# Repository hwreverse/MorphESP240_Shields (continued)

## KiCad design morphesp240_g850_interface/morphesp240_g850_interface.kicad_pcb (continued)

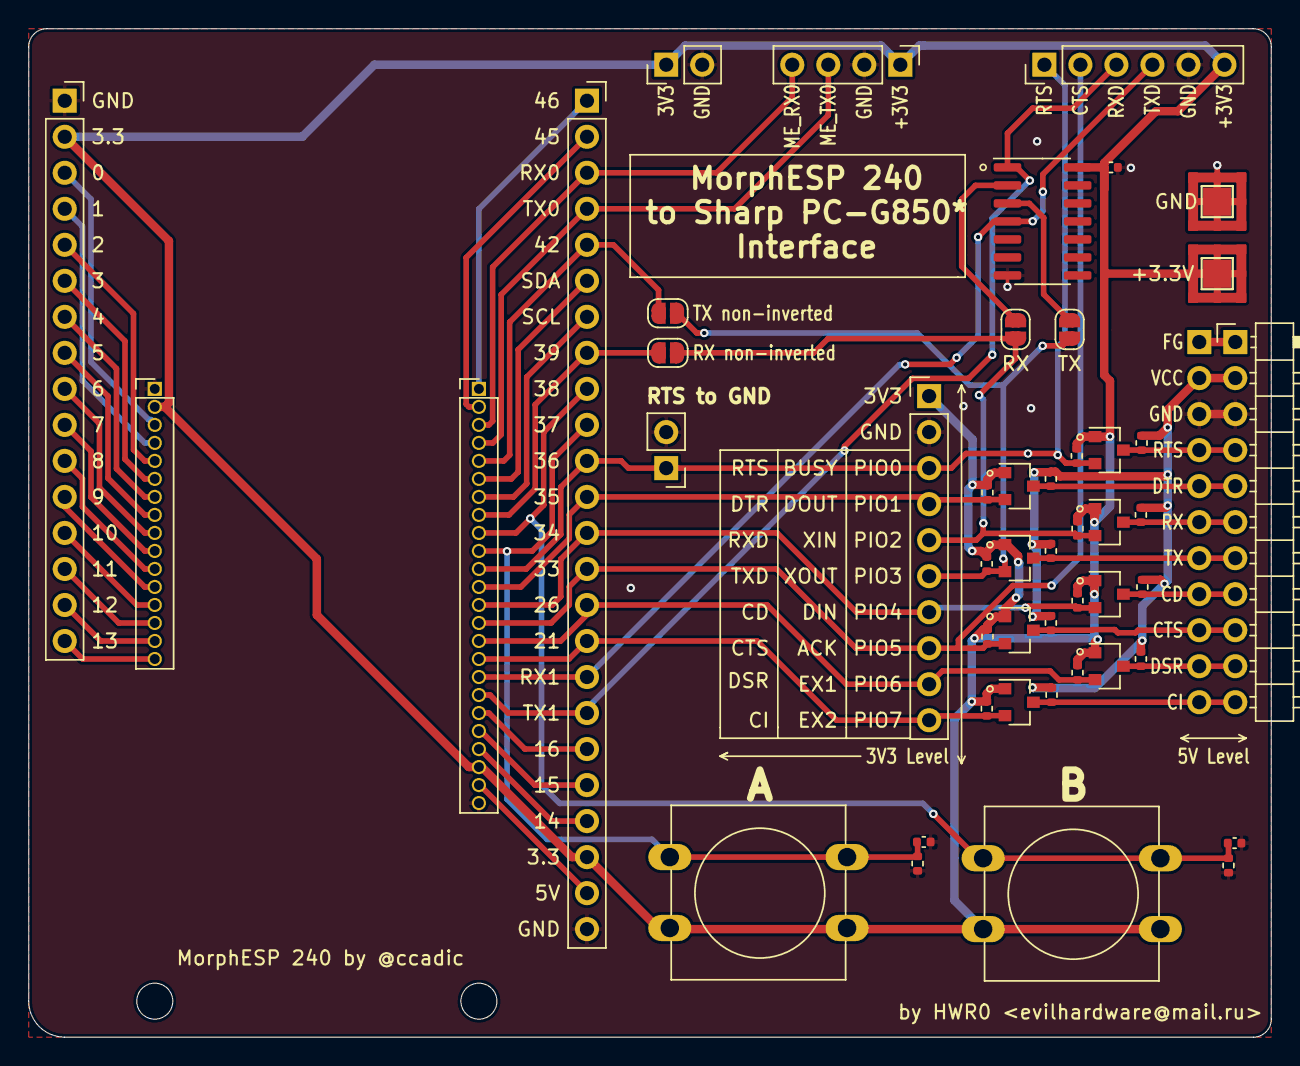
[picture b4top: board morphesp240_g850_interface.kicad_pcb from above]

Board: 2 copper layers, 87.6 x 71.1 mm, 49 parts (0 on the bottom side), 52 nets.

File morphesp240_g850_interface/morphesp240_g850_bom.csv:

Comment,Designator,Footprint,LCSC
"100nF","C1,C2,C3","Capacitor_SMD:C_0402_1005Metric","C1525"
"2.54P CNX","J1","Connector_PinSocket_2.54mm:PinSocket_1x24_P2.54mm_Vertical",""
"Conn_01x10_Male","J10","Connector_PinHeader_2.54mm:PinHeader_1x10_P2.54mm_Vertical",""
"3.3V Calculator Serial Output","J11","Connector_PinHeader_2.54mm:PinHeader_1x06_P2.54mm_Vertical",""
"CNDup","J12","hwreverse:BreadBoard_2.54mm_1x11",""
"Conn_01x11_Male","J13","Connector_PinHeader_2.54mm:PinHeader_1x11_P2.54mm_Horizontal",""
"1.27P CNX","J2","Socket_Strips:Socket_Strip_Straight_1x24_Pitch1.27mm",""
"1.27P CNX","J3","Socket_Strips:Socket_Strip_Straight_1x16_Pitch1.27mm",""
"2.54P CNX","J4","Connector_PinSocket_2.54mm:PinSocket_1x16_P2.54mm_Vertical",""
"3.3V Connector","J6","Connector_PinHeader_2.54mm:PinHeader_1x02_P2.54mm_Vertical",""
"SolidPad-Connector","J5,J7","hwreverse:SolidPad_4x4mm_2x2mmCore",""
"Conn_01x04_Male","J8","Connector_PinHeader_2.54mm:PinHeader_1x04_P2.54mm_Vertical",""
"RTS to Ground Jumper","J9","Connector_PinHeader_2.54mm:PinHeader_1x02_P2.54mm_Vertical",""
"SolderJumper_2_Open","JPRXD1,JPTXD1,JPLTXD1,JPLRXD1","Jumper:SolderJumper-2_P1.3mm_Open_RoundedPad1.0x1.5mm",""
"BSS138","Q1,Q2,Q3,Q4,Q5,Q6,Q7,Q8","Package_TO_SOT_SMD:SOT-23","C52895"
"10K","R1,R2,R3,R4,R5,R6,R7,R8,R9,R10,R11,R12,R13,R14,R15,R16,R17,R18","Resistor_SMD:R_0402_1005Metric","C25744"
"Button A","SW1","Button_Switch_THT:SW_PUSH-12mm","C620359"
"Button B","SW2","Button_Switch_THT:SW_PUSH-12mm","C620359"
"74HC04D","U1","Package_SO:SOIC-14_3.9x8.7mm_P1.27mm","C5590"

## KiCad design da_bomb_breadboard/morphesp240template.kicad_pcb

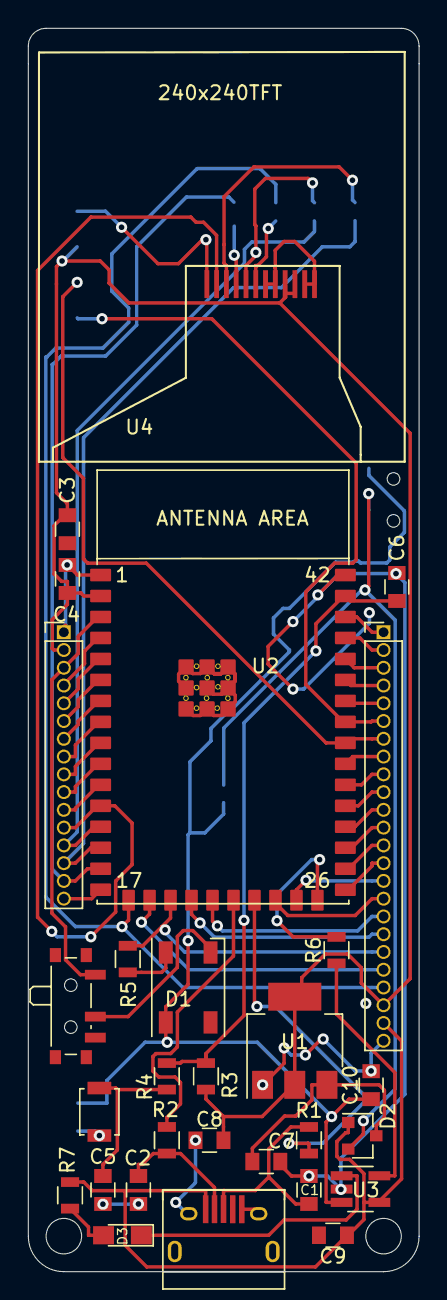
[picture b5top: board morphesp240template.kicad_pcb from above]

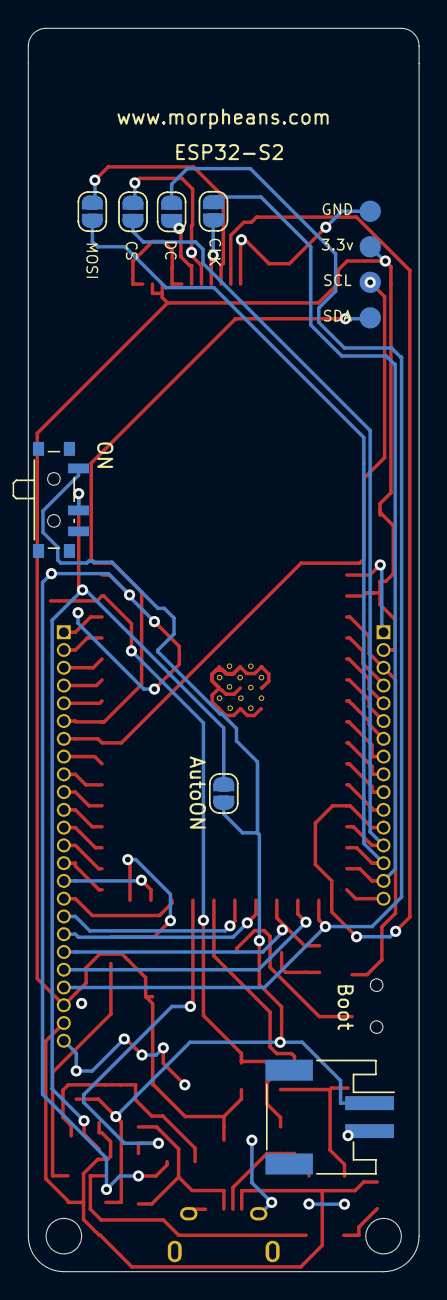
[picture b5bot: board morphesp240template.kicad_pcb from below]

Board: 2 copper layers, 27.9 x 88.9 mm, 37 parts (8 on the bottom side), 55 nets.

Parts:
C1, C2: 20pF; C_0805
C3, C5, C6: 100nF; C_0805
C4, C7, C8: 10uF; C_0805
C9, C10: 4.7uF; C_0805
D1: WS2812B; LED_WS2812B-PLCC4
D2: BAT54C; SOT-23
D3: Charge; LED_0805_HandSoldering
J1: USB_B_Mini; USB_Micro-B_HandSoldering
J2: Cnx1; Socket_Strip_Straight_1x16_Pitch1.27mm
J3: Con2; Socket_Strip_Straight_1x24_Pitch1.27mm
J4: Conn_01x02_Female; JST_PH_S2B-PH-SM4-TB_02x2.00mm_Angled
J5: i2C-v; 4cnx
JP1: CLK; JumperSmall
JP2: CS; JumperSmall
JP3: DC; JumperSmall
JP4: MOSI; JumperSmall
JP5: AutoON; JumperSmall
R1, R2, R4: 0R; R_0805
R3: 10k; R_0805
R5: 470; R_0805
R6: 2k; R_0805
R7: 470R; R_0805
SW1: SW_Push; SW_SPST_B3U-1000P
SW2: Boot; SW_SPDT_PCM12
SW3: ON; SW_SPDT_PCM12
U1: AP1117-33; SOT-223-3_TabPin2
U2: esp32-s2-wroom; esp32-s2-wrooom
U3: MCP73831-2-OT; SOT-23-5_HandSoldering
U4: 240x240TFT; 240240TFT

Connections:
/3.3v: C3.2, C4.2, C8.2, J2.2, J3.22, J5.3, R3.1, U1.2, U2.2, U4.3, U4.4
/D+: R1.1, U2.23
/D-: R2.1, U2.22
/DC_DISP: J3.21, JP3.1, U2.17
/EN: C6.2, R3.2, R4.1, U2.41
/IO0: J2.3, SW2.1, U2.3
/RGBLED: J3.19, R5.2, U2.19
/SCL: J3.7, J5.2, U2.34
/SDA: J3.6, J5.1, U2.35
/SPI_CLK: J2.15, JP1.1, U2.15
/SPI_CS: J2.13, JP2.1, U2.13
/SPI_MISO: J2.16, U2.16
/SPI_MOSI: J2.14, JP4.1, U2.14
/TFT_RESET: J2.12, U2.12, U4.11
/U1RXD: J3.17, U2.21
/U1TXD: J3.18, U2.20
/VBAT: C10.1, D1.1, J4.1, JP5.2, SW3.1, U3.3
/VUSB: C9.1, D2.1, J1.1, J3.23, R7.1, U3.4
GND: C1.2, C2.2, C3.1, C4.1, C5.2, C6.1, C7.1, C8.1, C9.2, C10.2, D1.3, J1.5, J1.6, J2.1, J3.24, J4.2, J5.4, R6.2, SW1.1, SW2.2, U1.1, U2.1, U2.26, U2.42, U2.43, U3.2, U4.1, U4.2, U4.5, U4.6, U4.12
unnamed: C1.1, J1.3, R1.2
unnamed: C2.1, J1.2, R2.2
unnamed: C5.1, R4.2, SW1.2
unnamed: C7.2, D2.3, U1.3
unnamed: D1.4, R5.1
unnamed: D2.2, JP5.1, SW3.2
unnamed: D3.1, U3.1
unnamed: D3.2, R7.2
unnamed: J2.4, U2.4
unnamed: J2.5, U2.5
unnamed: J2.6, U2.6
unnamed: J2.7, U2.7
unnamed: J2.8, U2.8
unnamed: J2.9, U2.9
unnamed: J2.10, U2.10
unnamed: J2.11, U2.11
unnamed: J3.1, U2.40
unnamed: J3.2, U2.39
unnamed: J3.3, U2.38
unnamed: J3.4, U2.37
unnamed: J3.5, U2.36
unnamed: J3.8, U2.33
unnamed: J3.9, U2.32
unnamed: J3.10, U2.31
unnamed: J3.11, U2.30
unnamed: J3.12, U2.29
unnamed: J3.13, U2.28
unnamed: J3.14, U2.27
unnamed: J3.15, U2.25
unnamed: J3.16, U2.24
unnamed: J3.20, U2.18
unnamed: JP1.2, U4.9
unnamed: JP2.2, U4.8
unnamed: JP3.2, U4.7
unnamed: JP4.2, U4.10
unnamed: R6.1, U3.5

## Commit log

2020-11-21 Update .gitignore to include BOM files
2020-11-21 Upload of unfinished first draft Da_Bomb Shield
2020-11-23 Added MorphESP 240 -G850 Interface
2020-11-24 Upload Gamepad Shield
2020-11-24 3 l are too much
2020-11-24 updated Schematic + pdf
2020-12-25 Added Gameshield 3D
2020-12-26 Added OPLL Sound Card Shield
2021-01-06 Added IRMaster
2021-01-06 corrected readme.md
2021-08-20 Updated 3D Shield with new KiCAD Project
2021-08-20 Updated Readme.md with data on 3DPad REV 2 !
2021-10-05 Fixing stupid inverted Schmitt Trigger
2021-10-07 Updated Gerber files + BOM + CPL
